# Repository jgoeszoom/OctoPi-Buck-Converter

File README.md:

# Buck Converter for OctoPi! 
A custom PCB implementation of the LM22678J-ADJ buck converter by Texas instruments. 

## Background
A popular upgrade for 3D printers is to use a Raspberry Pi running OctoPi 
to remotely slice, control, and monitor the printer. 

However, the popular method of powering the Raspberry Pi is using a buck converter
to stop the power from the PSU(24V) to 5V using the LM2596 buck converter. 
This popular regulator is readily available online but they have a big problem. 
They can always provide enough amperage to Raspberry Pi's, namely Raspberry Pi 4s. 

So I decided to make this implementation using the LM22678J-ADJ that can be set
to provide enough current at 5V. Using TI's Webench power designer I created the 
necessary supporting circuitry and simulated the circuit in LTSpice and made the PCB
in KiCAD. 

## Specifications

### To-do:

## Schematic

## PCB

## Render

## Bill-of-Materials

| References | Value | Footprint | Quantity |
| ---------- | ----- | --------- | -------- |
| R1, R2     | 10kOhms   | 0603      | 2        |
| L1         | 8.2uH | IHLP-2525 | 1        | 
| D1         | 440mV | SMC       | 1        |
| U1         | LM22678J-ADJ | -  | 1        |
| TP1-TP3    | Testpoint | 1.0mm hole | 3   |
| Cin1-Cin2  | 10uF  | 2220      | 2        |
| Cbst1      | 10nF  | 0805      | 1        |
| Cinx1      | 1uF   | 2220      | 1        |
| Cout1      | 100uF | 6.3x5.9mm | 1        |
| Rfb1       | 1kOhm | 0805      | 1        |
| Rfb2       | 3.01kOhm | 0603   | 1        |
| J1         | 1x2 Screw Terminal | P5.08mm | 1 |
| J2         | USB-C | -         | 1        |

In the iBOM directory is an HTML file that when opened shows a rendered 
view of the PCB next to the BOM. When you hover over BOM elements, the corresponding
part or trace is highlighted on the PCB.

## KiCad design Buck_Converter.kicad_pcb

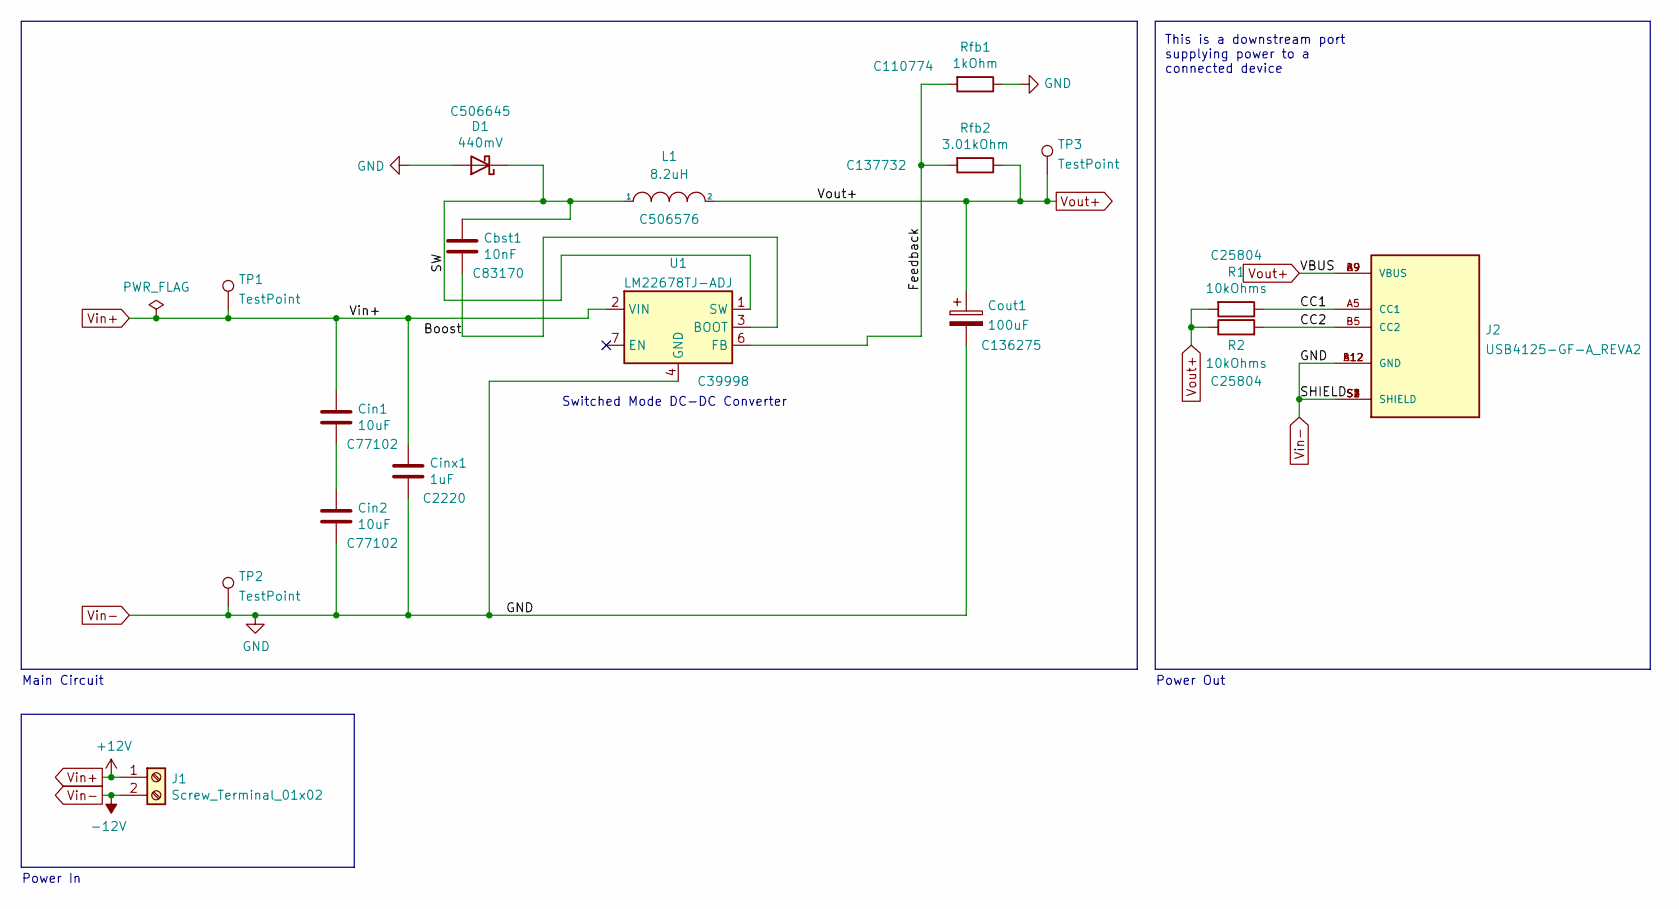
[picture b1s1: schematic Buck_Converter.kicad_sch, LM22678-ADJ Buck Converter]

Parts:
Cbst1: 10nF; C_0805_2012Metric; LCSC C83170
Cin1, Cin2: 10uF; C_1210_3225Metric; LCSC C77102
Cinx1: 1uF; C_2220_5650Metric; LCSC C2220
Cout1: 100uF; CP_Elec_6.3x5.9; LCSC C136275
D1: 440mV; D_SMC; LCSC C506645
J1: Screw_Terminal_01x02; TerminalBlock_bornier-2_P5.08mm
J2: USB4125-GF-A_REVA2; GCT_USB4125-GF-A_REVA2; PARTREV Rev A2
L1: 8.2uH; L_Vishay_IHLP-2525; LCSC C506576
R1, R2: 10kOhms; R_0603_1608Metric; LCSC C25804
Rfb1: 1kOhm; R_0805_2012Metric; LCSC C110774
Rfb2: 3.01kOhm; R_0603_1608Metric; LCSC C137732
TP1, TP2, TP3: TestPoint; TestPoint_Loop_D2.50mm_Drill1.0mm
U1: LM22678TJ-ADJ; LM22678TJE-ADJ&slash_NOPB; LCSC C39998

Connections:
/Boost: Cbst1.2, U1.3 (BOOT)
/CC1: J2.A5 (CC1), R1.1
/CC2: J2.B5 (CC2), R2.2
/Feedback: Rfb1.2, Rfb2.2, U1.6 (FB)
/SW: Cbst1.1, D1.1 (K), L1.1, U1.1 (SW)
unnamed: Cin1.2, Cin2.1
Vin+: Cin1.1, Cinx1.1, J1.1, TP1.1, U1.2 (VIN)
Vin-: Cin2.2, Cinx1.2, Cout1.2, D1.2 (A), J1.2, J2.A12 (GND), J2.B12 (GND), J2.S1 (SHIELD), J2.S2 (SHIELD), J2.S3 (SHIELD), J2.S4 (SHIELD), Rfb1.1, TP2.1, U1.4 (GND), U1.8 (GND)
Vout+: Cout1.1, J2.A9 (VBUS), J2.B9 (VBUS), L1.2, R1.2, R2.1, Rfb2.1, TP3.1

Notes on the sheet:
Switched Mode DC-DC Converter
Power In
This is a downstream port supplying power to a connected device
Power Out
Main Circuit

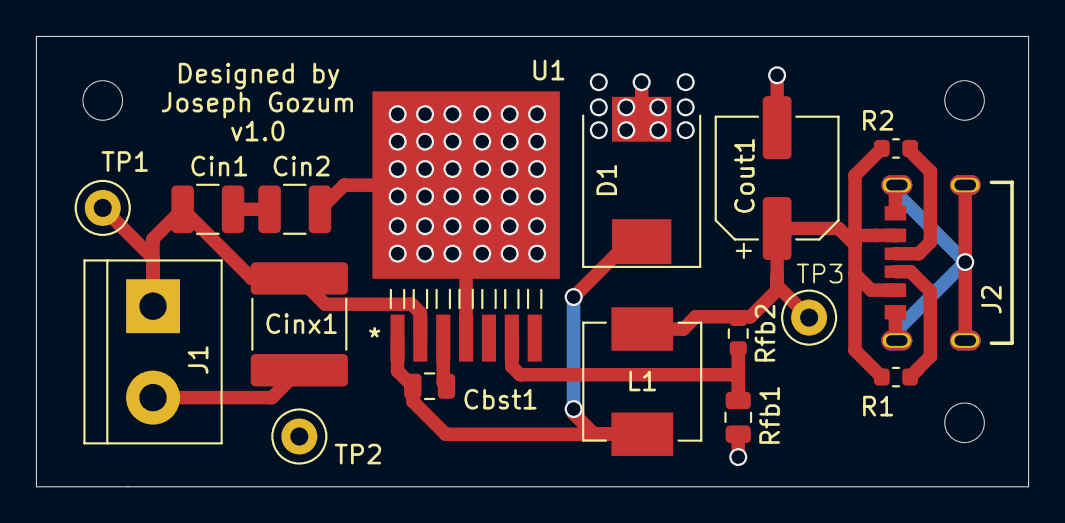
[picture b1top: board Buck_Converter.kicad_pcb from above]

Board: 2 copper layers, 55.1 x 25.0 mm, 20 parts (0 on the bottom side), 9 nets.

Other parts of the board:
REF1, REF2, REF3: MountingHole_2.2mm_M2

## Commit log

2022-01-31 Added README file and included some background for the project.
2022-01-31 Added Schematic image to README. Added PDF version of schematic.
2022-01-31 Updated gitignore to include zip and svg. Added PCB pdf.
2022-01-31 Added image of PCB in README
2022-01-31 Added Render of board to README
2022-01-31 Started ignoring zip files and old files from KiCAD 5.0
2022-01-31 Start ignoring Buck_Converter-bottom-pos.csv
2022-01-31 Started ignoring Buck_Converter.svg
2022-01-31 Added Bill-of-Materials section in README

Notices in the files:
parts and their libraries:
Copyright 2021 Accelerated Designs. All rights reserved.
